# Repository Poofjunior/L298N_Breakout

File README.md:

#A quick-n-simple L298N breakout board.

## Usage
To etch this circuit board through the toner-transfer method, go to the board 
view and deselect all layers except for 'bottom', 'pads', and 'vias'.  Then 
print (unmirrored) the existing view at 100% scale onto HP photo paper.  

##A few notes:  
I haven't yet added the parts list.  
This breakout does not break out the current-sensing pins. The end-goal is to 
quickly etch (or mill) 4 of these to drive stepper motors.

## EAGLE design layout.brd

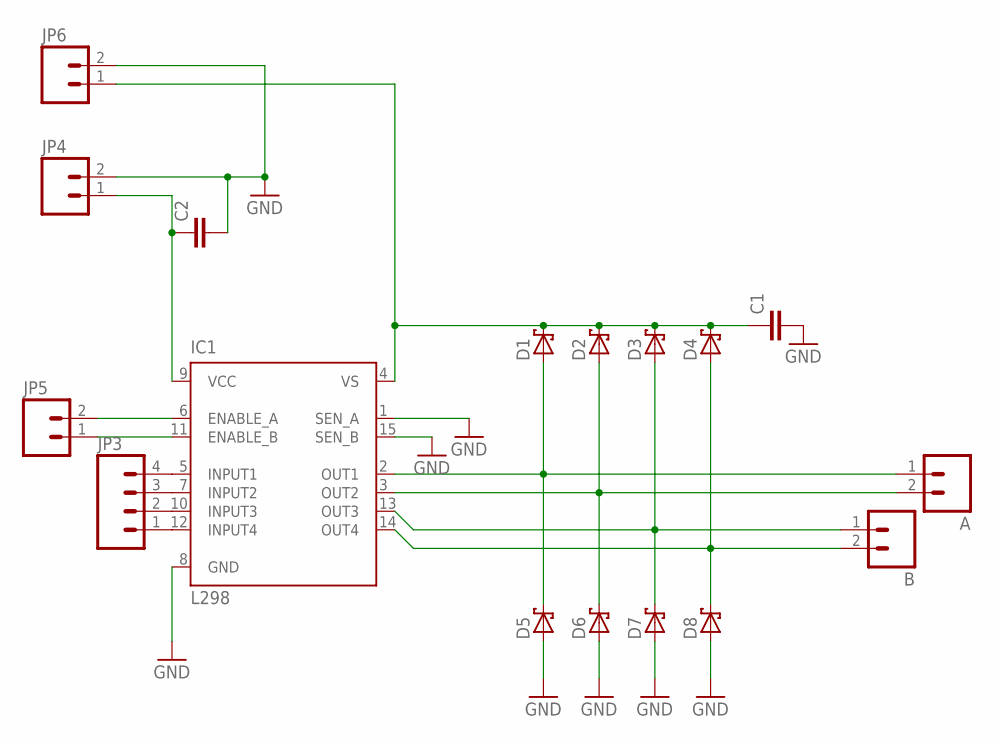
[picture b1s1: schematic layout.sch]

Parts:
A: M02PTH4; 1X02_XTRA_BIG
B: M02PTH4; 1X02_XTRA_BIG
C1, C2: C2,5-3; C2.5-3
D1, D2, D3, D4, D5, D6, D7, D8: SCHOTTKY-DIODEF126Z12; F126Z12
IC1: L298; MULTIWATT-15
JP3: M04POLAR; MOLEX-1X4
JP4, JP6: M021X02_NO_SILK; 1X02_NO_SILK
JP5: M02PTH; 1X02

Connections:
GND: C1.2, C2.2, D5.A, D6.A, D7.A, D8.A, IC1.1 (SEN_A), IC1.8 (GND), IC1.15 (SEN_B), JP4.2, JP6.2
unnamed: IC1.12 (INPUT4), JP3.1
unnamed: IC1.10 (INPUT3), JP3.2
unnamed: A.1, D1.A, D5.C, IC1.2 (OUT1)
unnamed: A.2, D2.A, D6.C, IC1.3 (OUT2)
unnamed: B.1, D3.A, D7.C, IC1.13 (OUT3)
unnamed: B.2, D4.A, D8.C, IC1.14 (OUT4)
unnamed: IC1.7 (INPUT2), JP3.3
unnamed: IC1.5 (INPUT1), JP3.4
unnamed: C1.1, D1.C, D2.C, D3.C, D4.C, IC1.4 (VS), JP6.1
unnamed: C2.1, IC1.9 (VCC), JP4.1
unnamed: IC1.11 (ENABLE_B), JP5.1
unnamed: IC1.6 (ENABLE_A), JP5.2

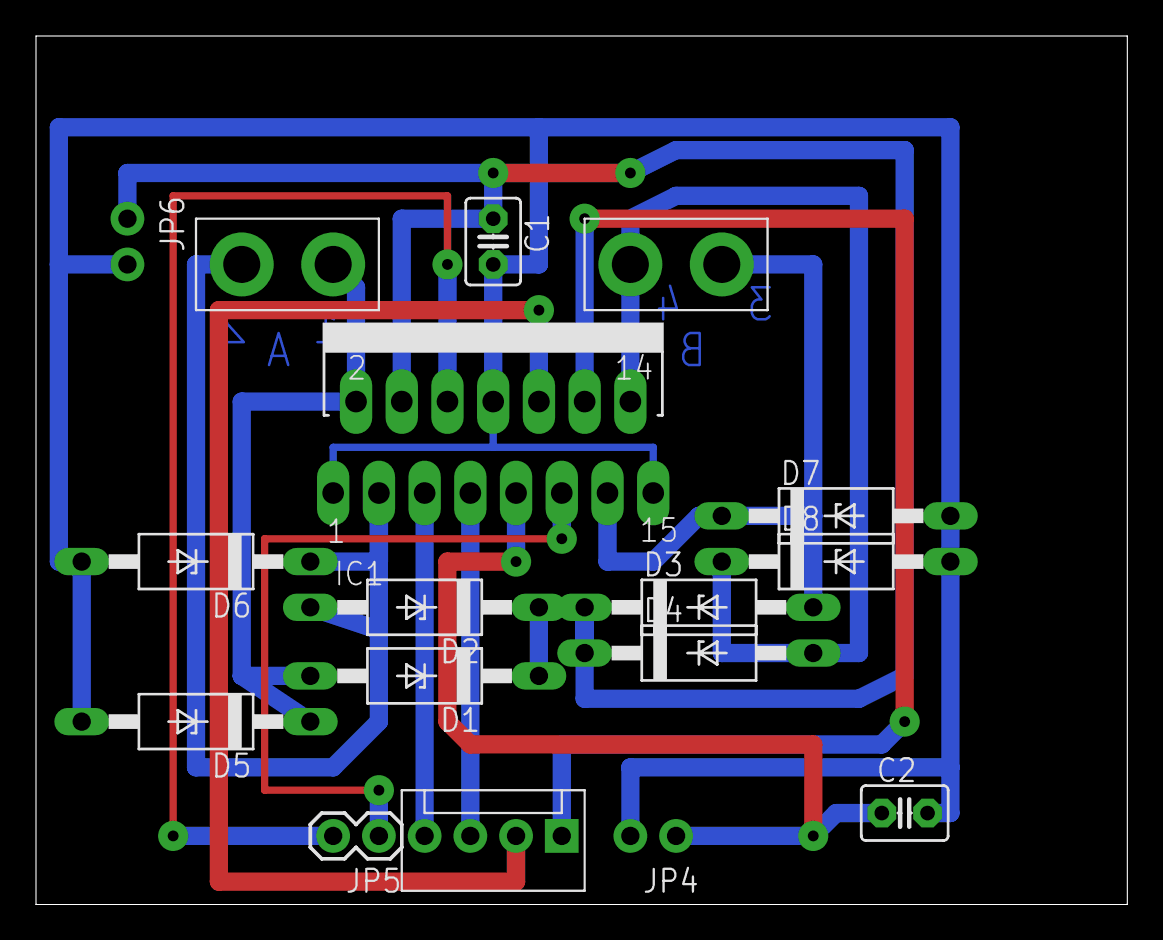
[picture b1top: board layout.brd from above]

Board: 2 copper layers, 60.6 x 48.2 mm, 17 parts (0 on the bottom side), 13 nets.

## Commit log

2013-01-14 updated readme with basic usage instructions
2013-02-22 added the gitignore file

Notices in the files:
parts and their libraries:
SparkFun-Connectors: Licensing: CC v3.0 Share-Alike You are welcome to use this library for commercial purposes.
